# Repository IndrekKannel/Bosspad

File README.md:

# Bosspad  

I designed a 9 key and 1 encoder macropad for the real bosses. It also has an OLED screen and is designed to be mouted on a vertical surface.  
I plan on using it as a button box for sim racing. 
It uses QMK firmware and supports VIA

## PCB

I designed the PCB with KiCad

## Case

I designed the case in Fusion360 and it can be printed in 2 parts.  
It is assembled with 4 M3x16 screws and 4 M3x5x4mm heatset inserts.

## BOM

### PCB

- 1x Seeed Studio Xiao RP2040
- 1x EC11E Rotary Encoder (switch built in)
- 1x rotary Encoder Knob (can also be printed)
- 1x 0.91" SSD1306 OLED screen
- 9x Cherry MX style switches
- 9x Blank DSA keycaps
- 10x DO-35 diodes (THT)

### Case

- 4x M3x16mm socket head bolts
- 4x M3x5x4mm heatset inserts
- bosspad_top.step
- bosspad_bottom.step

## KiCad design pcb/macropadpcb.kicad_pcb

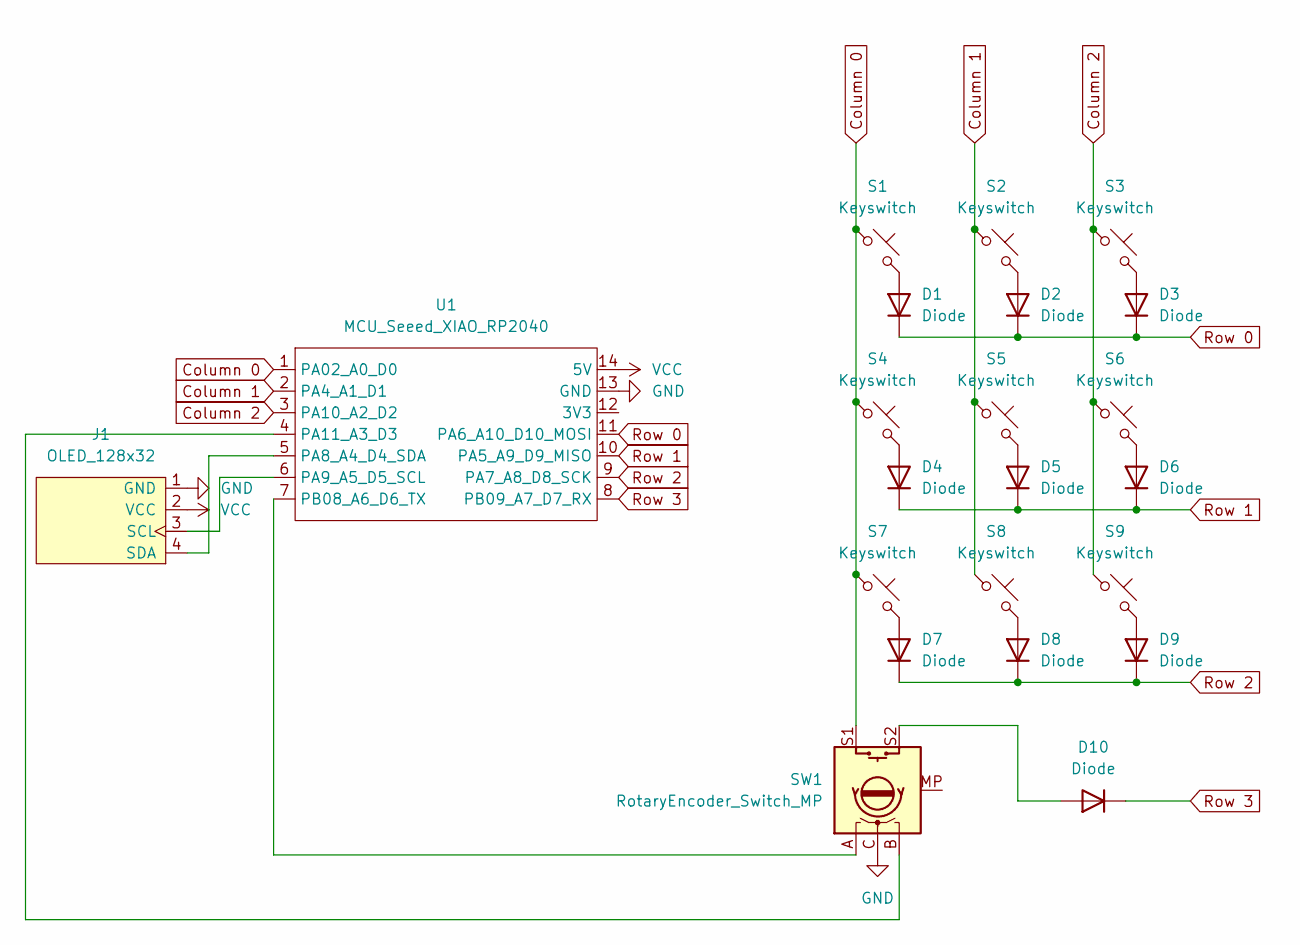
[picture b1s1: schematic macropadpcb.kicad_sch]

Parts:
D1, D2, D3, D4, D5, D6, D7, D8, D9, D10: Diode; Diode_DO-35
J1: OLED_128x32
S1, S2, S3, S4, S5, S6, S7, S8, S9: Keyswitch; MX_PCB_1.00u
SW1: RotaryEncoder_Switch_MP; RotaryEncoder_Alps_EC11E-Switch_Vertical_H20mm_MountingHoles
U1: MCU_Seeed_XIAO_RP2040; Seeed_XIAO_RP2040

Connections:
Column 0: S1.1, S4.1, S7.1, SW1.S1, U1.1 (PA02_A0_D0)
Column 1: S2.1, S5.1, S8.1, U1.2 (PA4_A1_D1)
Column 2: S3.1, S6.1, S9.1, U1.3 (PA10_A2_D2)
GND: J1.1 (GND), SW1.C, U1.13 (GND)
unnamed: D1.2 (A), S1.2
unnamed: D2.2 (A), S2.2
unnamed: D3.2 (A), S3.2
unnamed: D4.2 (A), S4.2
unnamed: D5.2 (A), S5.2
unnamed: D6.2 (A), S6.2
unnamed: D7.2 (A), S7.2
unnamed: D8.2 (A), S8.2
unnamed: D9.2 (A), S9.2
unnamed: D10.2 (A), SW1.S2
unnamed: J1.3 (SCL), U1.6 (PA9_A5_D5_SCL)
unnamed: J1.4 (SDA), U1.5 (PA8_A4_D4_SDA)
unnamed: SW1.B, U1.4 (PA11_A3_D3)
unnamed: SW1.A, U1.7 (PB08_A6_D6_TX)
Row 0: D1.1 (K), D2.1 (K), D3.1 (K), U1.11 (PA6_A10_D10_MOSI)
Row 1: D4.1 (K), D5.1 (K), D6.1 (K), U1.10 (PA5_A9_D9_MISO)
Row 2: D7.1 (K), D8.1 (K), D9.1 (K), U1.9 (PA7_A8_D8_SCK)
Row 3: D10.1 (K), U1.8 (PB09_A7_D7_RX)
VCC: J1.2 (VCC), U1.14 (5V)

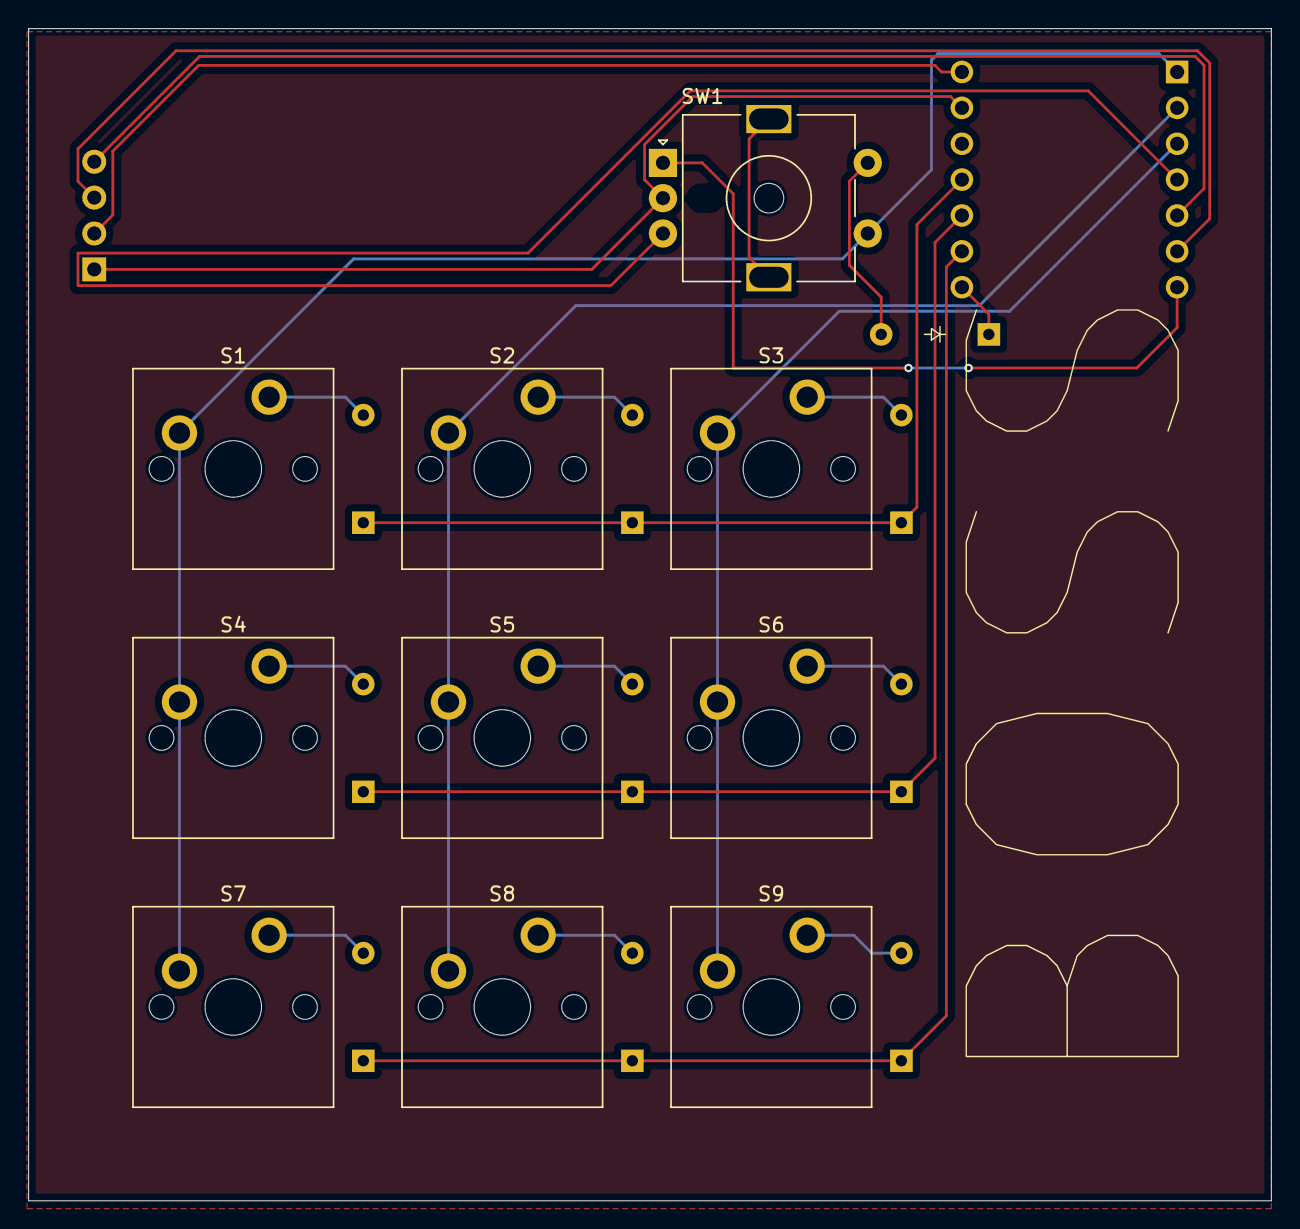
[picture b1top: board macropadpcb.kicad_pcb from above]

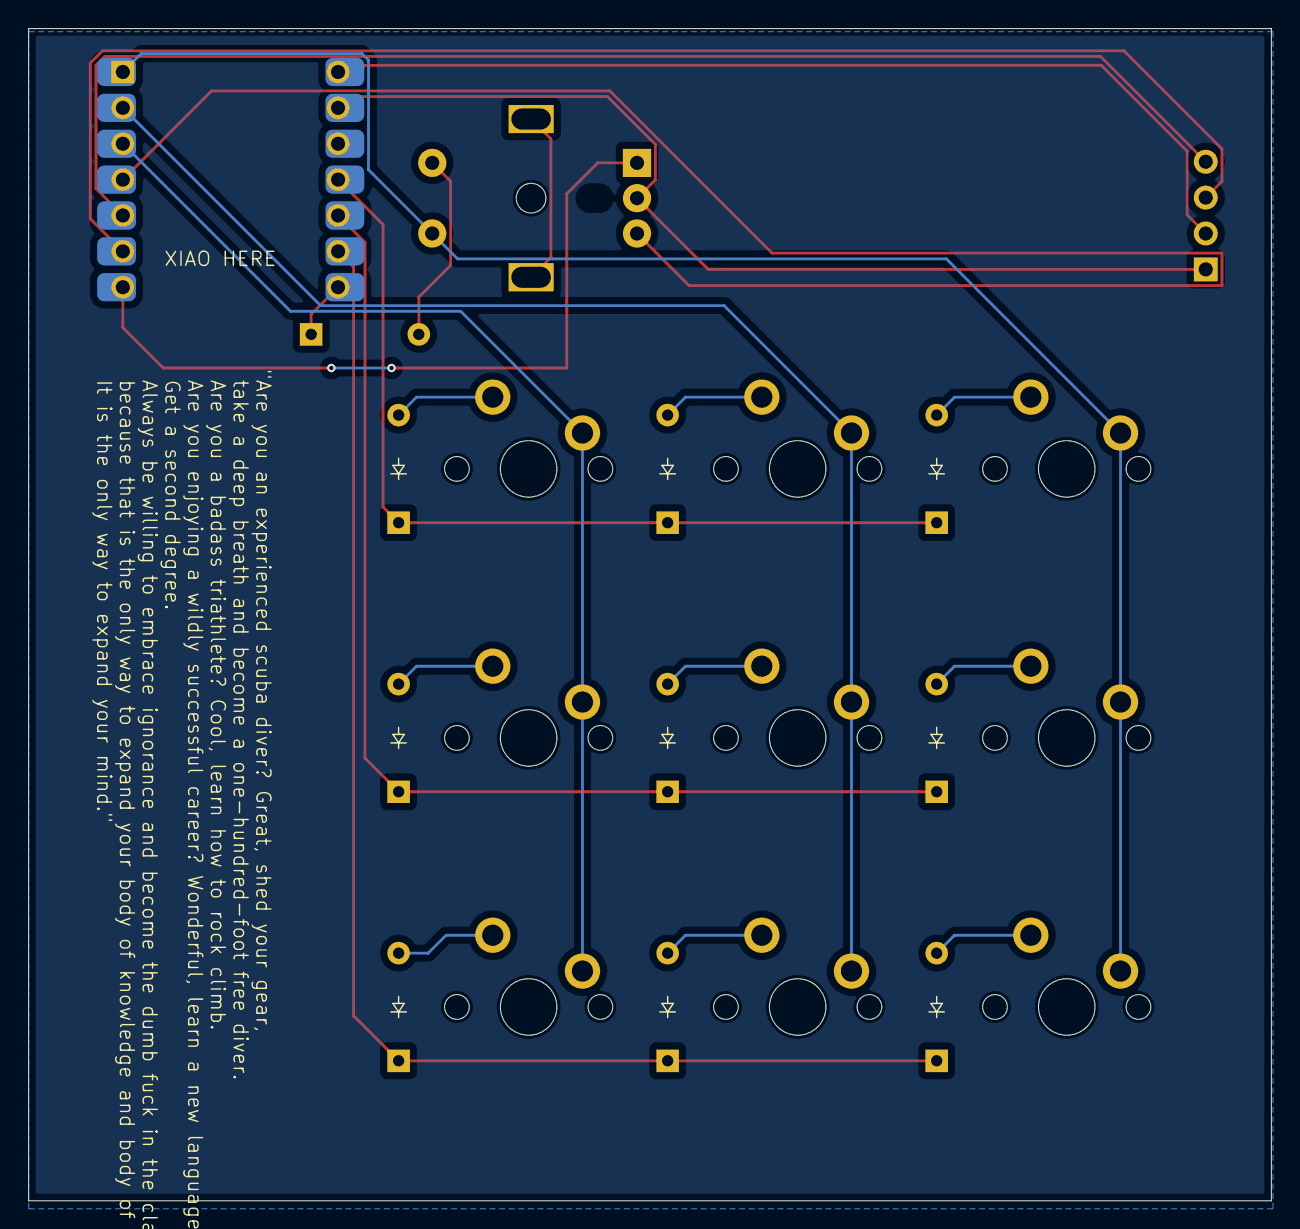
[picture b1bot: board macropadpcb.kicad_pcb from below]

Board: 2 copper layers, 88.0 x 83.0 mm, 22 parts (10 on the bottom side), 23 nets.

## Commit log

2025-06-29 added files
2025-06-29 tried again
